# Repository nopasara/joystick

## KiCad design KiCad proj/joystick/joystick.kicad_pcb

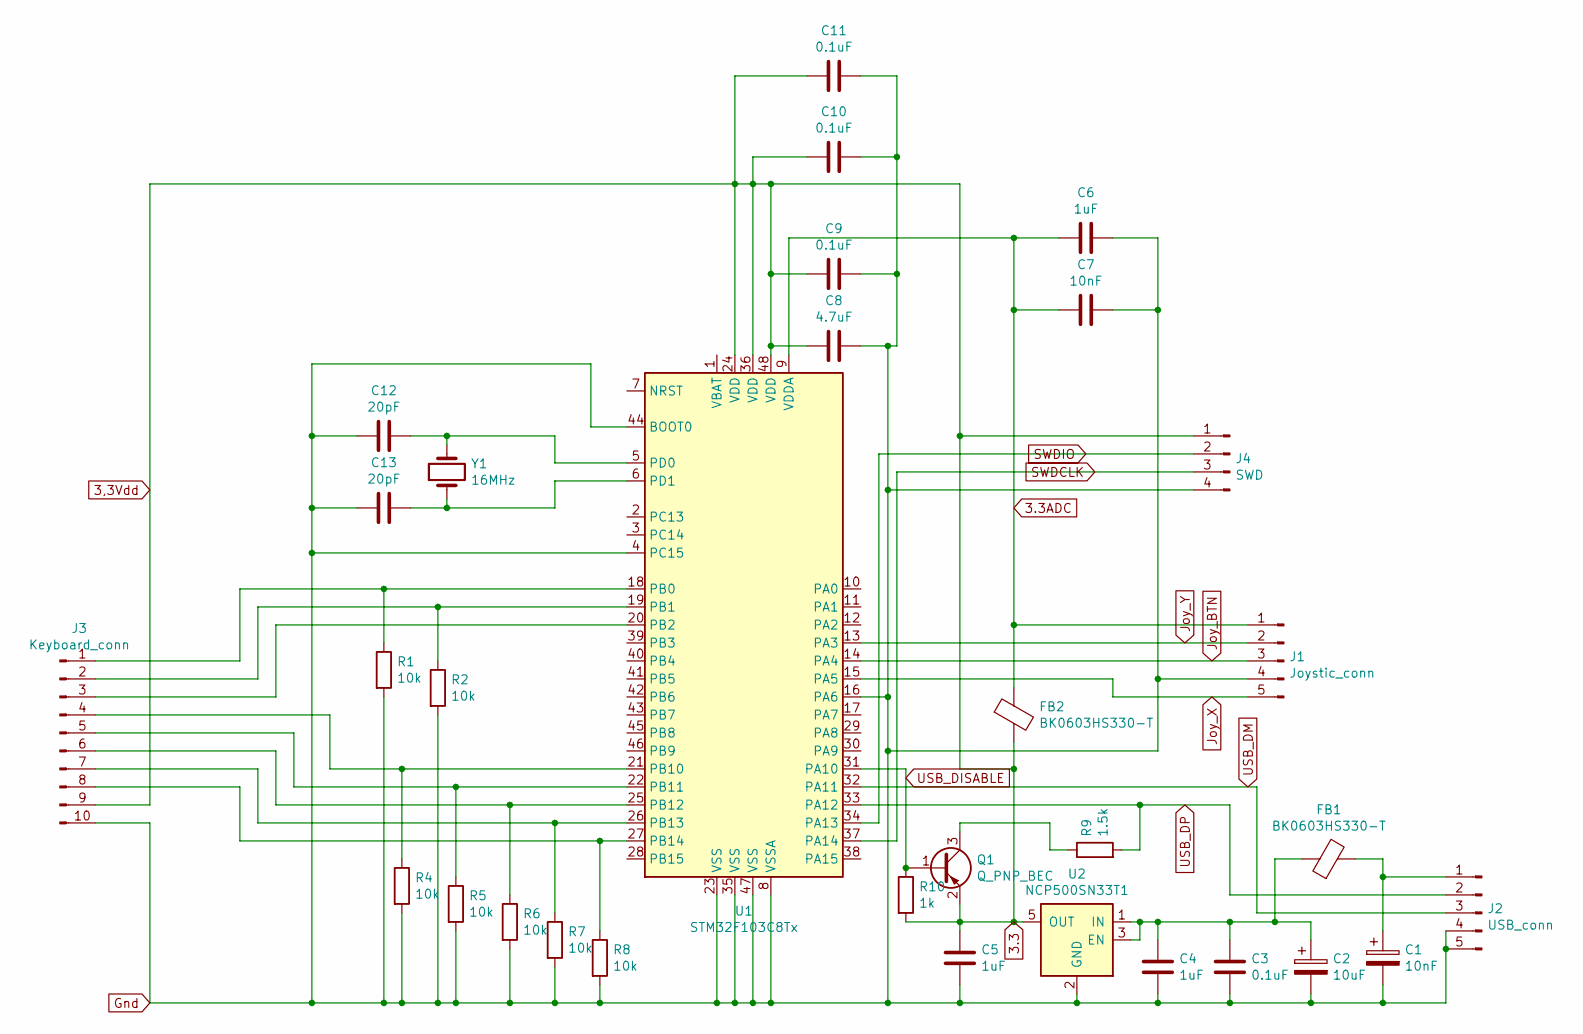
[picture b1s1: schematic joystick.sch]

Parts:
C1, C7: 10nF; C_0603_1608Metric_Pad1.08x0.95mm_HandSolder
C2: 10uF; CP_Radial_D5.0mm_P2.50mm
C3, C9, C10, C11: 0.1uF; C_0805_2012Metric_Pad1.18x1.45mm_HandSolder
C4, C5, C6: 1uF; C_0805_2012Metric_Pad1.18x1.45mm_HandSolder
C8: 4.7uF; CP_Radial_D5.0mm_P2.50mm
C12, C13: 20pF; C_0603_1608Metric_Pad1.08x0.95mm_HandSolder
FB1, FB2: BK0603HS330-T; R_0603_1608Metric_Pad0.98x0.95mm_HandSolder
J1: Joystic_conn; FPC-5P-0.5mm
J2: USB_conn; PinHeader_1x05_P2.54mm_Vertical
J3: Keyboard_conn; Hirose_FH12-10S-0.5SH_1x10-1MP_P0.50mm_Horizontal
J4: SWD; PinHeader_1x04_P2.54mm_Vertical
Q1: Q_PNP_BEC; SOT-23
R1, R2, R4, R5, R6, R7, R8: 10k; R_0201_0603Metric_Pad0.64x0.40mm_HandSolder
R9: 1.5k; C_0805_2012Metric_Pad1.18x1.45mm_HandSolder
R10: 1k; R_0603_1608Metric_Pad0.98x0.95mm_HandSolder
U1: STM32F103C8Tx; LQFP-48_7x7mm_P0.5mm
U2: NCP500SN33T1; TSOP-5_1.65x3.05mm_P0.95mm
Y1: 16MHz; Crystal_HC49-S_Vertical

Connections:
3,3Vdd: C5.1, C8.1, C9.1, C10.1, C11.1, FB2.2, J3.9, J4.1, Q1.2 (E), R10.2, U1.24 (VDD), U1.36 (VDD), U1.48 (VDD), U2.5 (OUT)
3.3ADC: C6.1, C7.1, FB2.1, J1.1, U1.9 (VDDA)
Gnd: C1.2, C2.2, C3.2, C4.2, C5.2, C6.2, C7.2, C8.2, C9.2, C10.2, C11.2, C12.1, C13.1, J1.4, J2.4, J2.5, J3.10, J4.4, R1.2, R2.2, R4.2, R5.2, R6.2, R7.2, R8.2, U1.4 (PC15), U1.8 (VSSA), U1.16 (PA6), U1.23 (VSS), U1.35 (VSS), U1.44 (BOOT0), U1.47 (VSS), U2.2 (GND)
Joy_BTN: J1.3, U1.14 (PA4)
Joy_X: J1.5, U1.15 (PA5)
Joy_Y: J1.2, U1.13 (PA3)
unnamed: C1.1, FB1.2, J2.1
unnamed: C2.1, C3.1, C4.1, FB1.1, U2.1 (IN), U2.3 (EN)
unnamed: C12.2, U1.5 (PD0), Y1.2
unnamed: C13.2, U1.6 (PD1), Y1.1
unnamed: J3.1, R1.1, U1.18 (PB0)
unnamed: J3.2, R2.1, U1.19 (PB1)
unnamed: J3.3, U1.20 (PB2)
unnamed: J3.4, R4.1, U1.21 (PB10)
unnamed: J3.5, R5.1, U1.22 (PB11)
unnamed: J3.6, R6.1, U1.25 (PB12)
unnamed: J3.7, R7.1, U1.26 (PB13)
unnamed: J3.8, R8.1, U1.27 (PB14)
unnamed: Q1.3 (C), R9.1
SWDCLK: J4.3, U1.37 (PA14)
SWDIO: J4.2, U1.34 (PA13)
USB_DISABLE: Q1.1 (B), R10.1, U1.31 (PA10)
USB_DM: J2.3, U1.32 (PA11)
USB_DP: J2.2, R9.2, U1.33 (PA12)

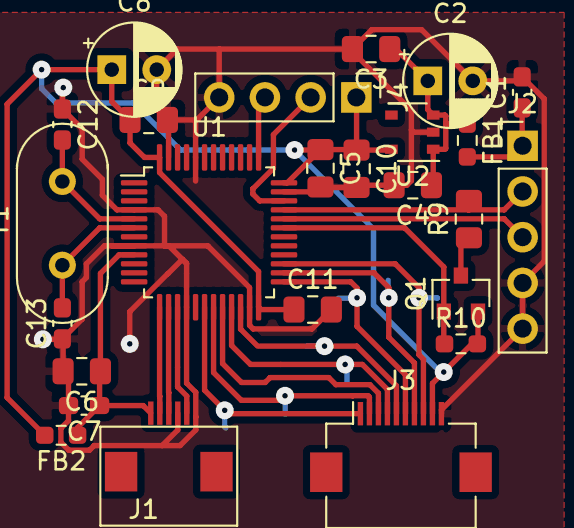
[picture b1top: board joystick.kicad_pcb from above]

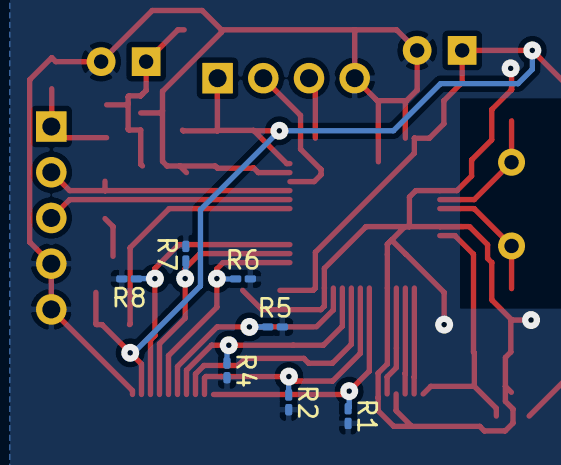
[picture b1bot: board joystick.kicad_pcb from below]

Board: 2 copper layers, 32 parts (7 on the bottom side), 24 nets.

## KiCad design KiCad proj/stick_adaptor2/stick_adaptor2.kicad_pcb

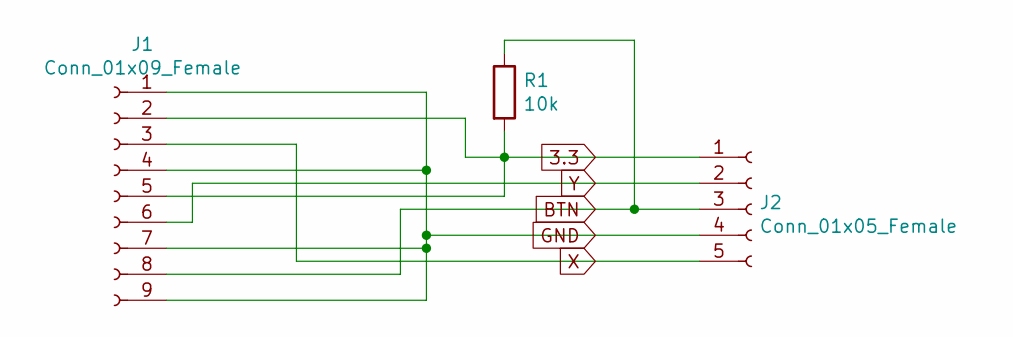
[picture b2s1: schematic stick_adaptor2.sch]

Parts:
J1: Conn_01x09_Female; Stick_china
J2: Conn_01x05_Female; PinHeader_1x05_P1.27mm_Vertical
R1: 10k; R_0603_1608Metric_Pad0.98x0.95mm_HandSolder

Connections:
3.3: J1.2, J1.5, J2.1, R1.2
BTN: J1.8, J2.3, R1.1
GND: J1.1, J1.4, J1.7, J1.9, J2.4
X: J1.3, J2.5
Y: J1.6, J2.2

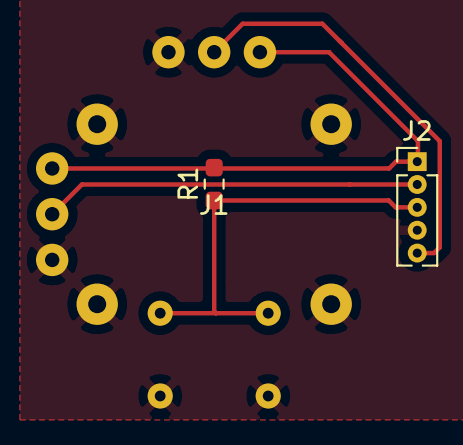
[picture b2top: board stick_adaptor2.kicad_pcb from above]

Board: 2 copper layers, 3 parts (0 on the bottom side), 5 nets.

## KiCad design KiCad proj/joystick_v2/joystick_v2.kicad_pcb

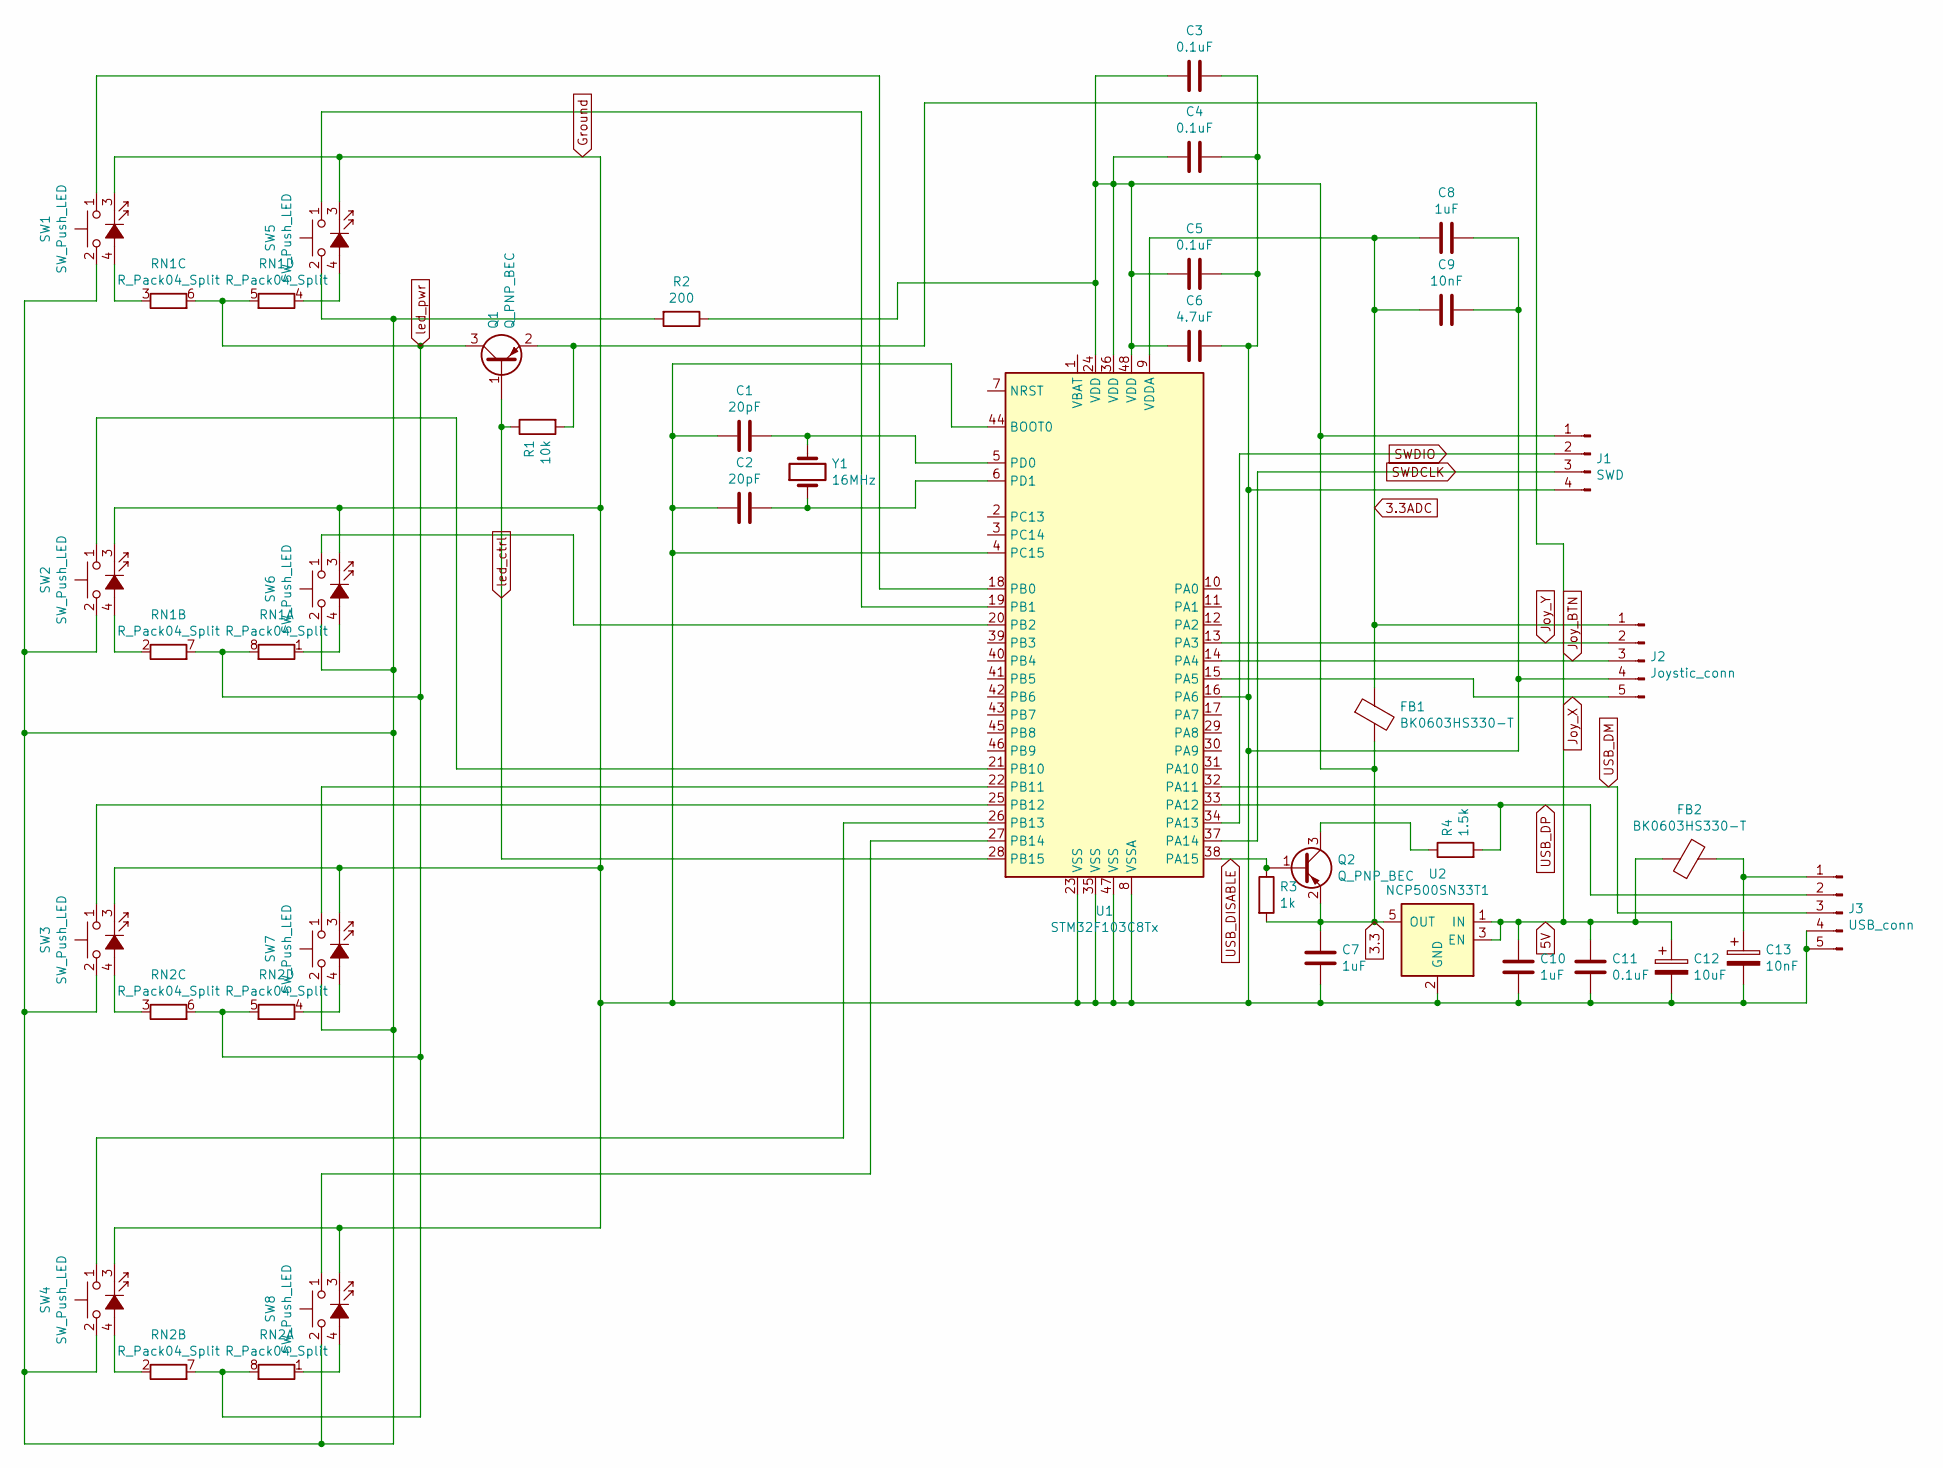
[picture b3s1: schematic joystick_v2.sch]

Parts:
C1, C2: 20pF; C_0603_1608Metric_Pad1.08x0.95mm_HandSolder
C3, C4, C5, C11: 0.1uF; C_0805_2012Metric_Pad1.18x1.45mm_HandSolder
C6: 4.7uF; CP_Radial_D5.0mm_P2.50mm
C7, C8, C10: 1uF; C_0805_2012Metric_Pad1.18x1.45mm_HandSolder
C9, C13: 10nF; C_0603_1608Metric_Pad1.08x0.95mm_HandSolder
C12: 10uF; CP_Radial_D5.0mm_P2.50mm
FB1, FB2: BK0603HS330-T; R_0603_1608Metric_Pad0.98x0.95mm_HandSolder
J1: SWD; PinHeader_1x04_P2.54mm_Vertical
J2: Joystic_conn; PinHeader_1x05_P1.27mm_Vertical
J3: USB_conn; PinHeader_1x05_P2.54mm_Vertical
Q1, Q2: Q_PNP_BEC; SOT-23
R1: 10k; R_0603_1608Metric_Pad0.98x0.95mm_HandSolder
R2: 200; R_0603_1608Metric_Pad0.98x0.95mm_HandSolder
R3: 1k; R_0603_1608Metric_Pad0.98x0.95mm_HandSolder
R4: 1.5k; C_0805_2012Metric_Pad1.18x1.45mm_HandSolder
RN1, RN2: R_Pack04_Split; R_Cat16-4
SW1, SW2, SW3, SW4, SW5, SW6, SW7, SW8: SW_Push_LED; SW_Cherry_MX_1.00u_Plate_diode
U1: STM32F103C8Tx; LQFP-48_7x7mm_P0.5mm
U2: NCP500SN33T1; TSOP-5_1.65x3.05mm_P0.95mm
Y1: 16MHz; Crystal_HC49-S_Vertical

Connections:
3.3: C3.1, C4.1, C5.1, C6.1, C7.1, FB1.2, J1.1, Q2.2 (E), R2.1, R3.2, U1.24 (VDD), U1.36 (VDD), U1.48 (VDD), U2.5 (OUT)
3.3ADC: C8.1, C9.1, FB1.1, J2.1, U1.9 (VDDA)
5V: C10.1, C11.1, C12.1, FB2.1, Q1.2 (E), R1.2, U2.1 (IN), U2.3 (EN)
Ground: C1.1, C2.1, C3.2, C4.2, C5.2, C6.2, C7.2, C8.2, C9.2, C10.2, C11.2, C12.2, C13.2, J1.4, J2.4, J3.4, J3.5, SW1.3 (K), SW2.3 (K), SW3.3 (K), SW4.3 (K), SW5.3 (K), SW6.3 (K), SW7.3 (K), SW8.3 (K), U1.4 (PC15), U1.8 (VSSA), U1.16 (PA6), U1.23 (VSS), U1.35 (VSS), U1.44 (BOOT0), U1.47 (VSS), U2.2 (GND)
Joy_BTN: J2.3, U1.14 (PA4)
Joy_X: J2.5, U1.15 (PA5)
Joy_Y: J2.2, U1.13 (PA3)
unnamed: C1.2, U1.5 (PD0), Y1.2
unnamed: C2.2, U1.6 (PD1), Y1.1
unnamed: C13.1, FB2.2, J3.1
unnamed: Q2.3 (C), R4.1
unnamed: R2.2, SW1.2, SW2.2, SW3.2, SW4.2, SW5.2, SW6.2, SW7.2, SW8.2
unnamed: RN1.1 (R1.1), SW6.4 (A)
unnamed: RN1.2 (R2.1), SW2.4 (A)
unnamed: RN1.3 (R3.1), SW1.4 (A)
unnamed: RN1.4 (R4.1), SW5.4 (A)
unnamed: RN2.1 (R1.1), SW8.4 (A)
unnamed: RN2.2 (R2.1), SW4.4 (A)
unnamed: RN2.3 (R3.1), SW3.4 (A)
unnamed: RN2.4 (R4.1), SW7.4 (A)
unnamed: SW1.1, U1.18 (PB0)
unnamed: SW2.1, U1.21 (PB10)
unnamed: SW3.1, U1.25 (PB12)
unnamed: SW4.1, U1.26 (PB13)
unnamed: SW5.1, U1.19 (PB1)
unnamed: SW6.1, U1.20 (PB2)
unnamed: SW7.1, U1.22 (PB11)
unnamed: SW8.1, U1.27 (PB14)
SWDCLK: J1.3, U1.37 (PA14)
SWDIO: J1.2, U1.34 (PA13)
USB_DISABLE: Q2.1 (B), R3.1, U1.38 (PA15)
USB_DM: J3.3, U1.32 (PA11)
USB_DP: J3.2, R4.2, U1.33 (PA12)
led_ctrl: Q1.1 (B), R1.1, U1.28 (PB15)
led_pwr: Q1.3 (C), RN1.5 (R4.2), RN1.6 (R3.2), RN1.7 (R2.2), RN1.8 (R1.2), RN2.5 (R4.2), RN2.6 (R3.2), RN2.7 (R2.2), RN2.8 (R1.2)

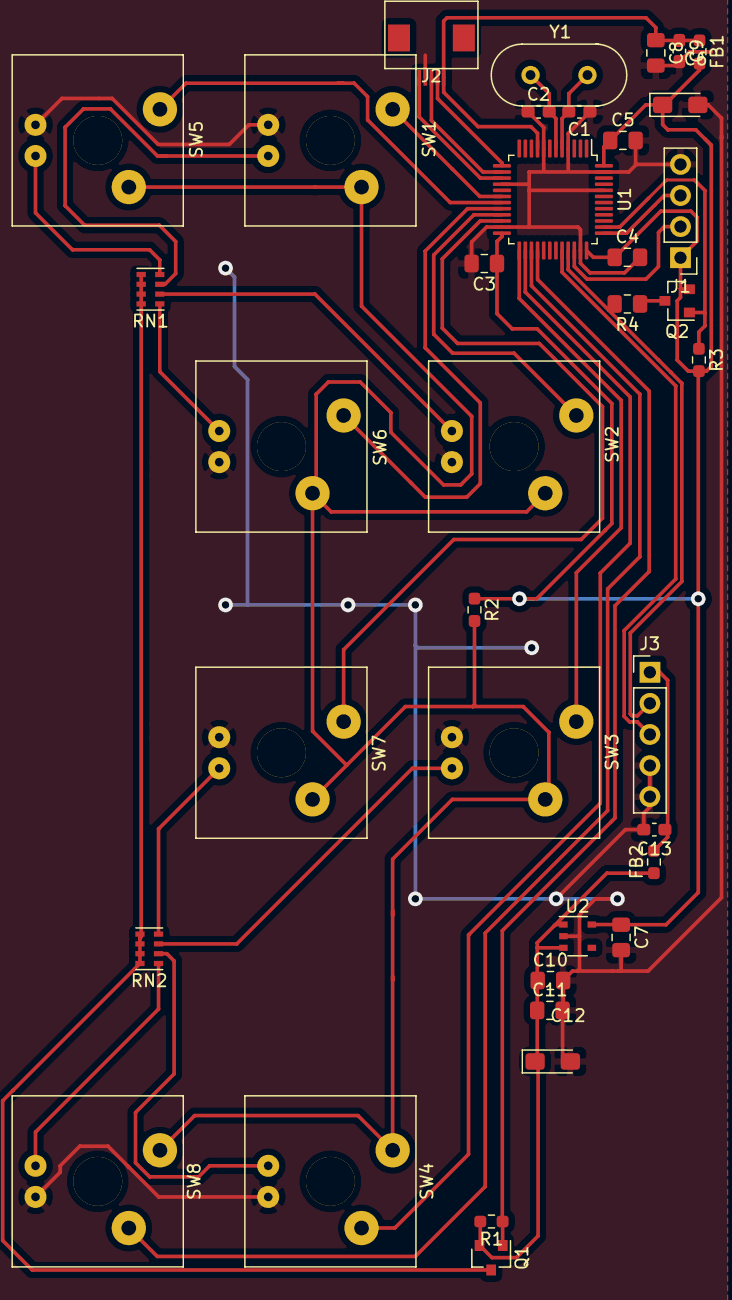
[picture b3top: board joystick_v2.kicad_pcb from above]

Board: 2 copper layers, 37 parts (0 on the bottom side), 35 nets.

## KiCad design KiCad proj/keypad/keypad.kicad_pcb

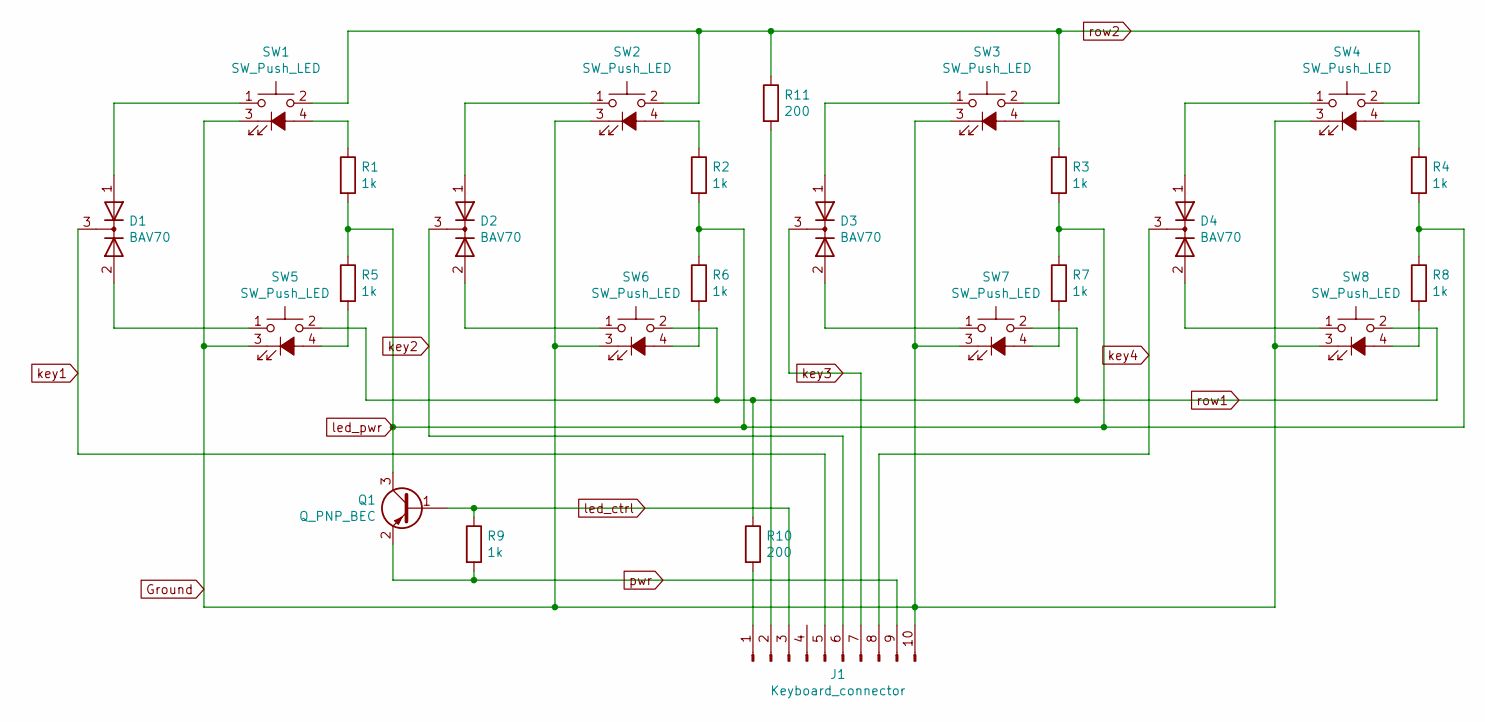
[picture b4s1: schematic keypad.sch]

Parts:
D1, D2, D3, D4: BAV70; SOT-23
J1: Keyboard_connector; Hirose_FH12-10S-0.5SH_1x10-1MP_P0.50mm_Horizontal
Q1: Q_PNP_BEC; SOT-23
R1, R2, R3, R4, R5, R6, R7, R8, R9: 1k; R_0603_1608Metric_Pad0.98x0.95mm_HandSolder
R10, R11: 200; R_0603_1608Metric_Pad0.98x0.95mm_HandSolder
SW1, SW2, SW3, SW4, SW5, SW6, SW7, SW8: SW_Push_LED; PinHeader_1x04_P2.54mm_Vertical

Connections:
Ground: J1.10, SW1.3 (K), SW2.3 (K), SW3.3 (K), SW4.3 (K), SW5.3 (K), SW6.3 (K), SW7.3 (K), SW8.3 (K)
unnamed: D1.1 (A), SW1.1
unnamed: D1.2 (A), SW5.1
unnamed: D2.1 (A), SW2.1
unnamed: D2.2 (A), SW6.1
unnamed: D3.1 (A), SW3.1
unnamed: D3.2 (A), SW7.1
unnamed: D4.1 (A), SW4.1
unnamed: D4.2 (A), SW8.1
unnamed: J1.1, R10.2
unnamed: J1.2, R11.2
unnamed: R1.1, SW1.4 (A)
unnamed: R2.1, SW2.4 (A)
unnamed: R3.1, SW3.4 (A)
unnamed: R4.1, SW4.4 (A)
unnamed: R5.2, SW5.4 (A)
unnamed: R6.2, SW6.4 (A)
unnamed: R7.2, SW7.4 (A)
unnamed: R8.2, SW8.4 (A)
key1: D1.3 (K), J1.5
key2: D2.3 (K), J1.6
key3: D3.3 (K), J1.7
key4: D4.3 (K), J1.8
led_ctrl: J1.3, Q1.1 (B), R9.1
led_pwr: Q1.3 (C), R1.2, R2.2, R3.2, R4.2, R5.1, R6.1, R7.1, R8.1
pwr: J1.9, Q1.2 (E), R9.2
row1: R10.1, SW5.2, SW6.2, SW7.2, SW8.2
row2: R11.1, SW1.2, SW2.2, SW3.2, SW4.2

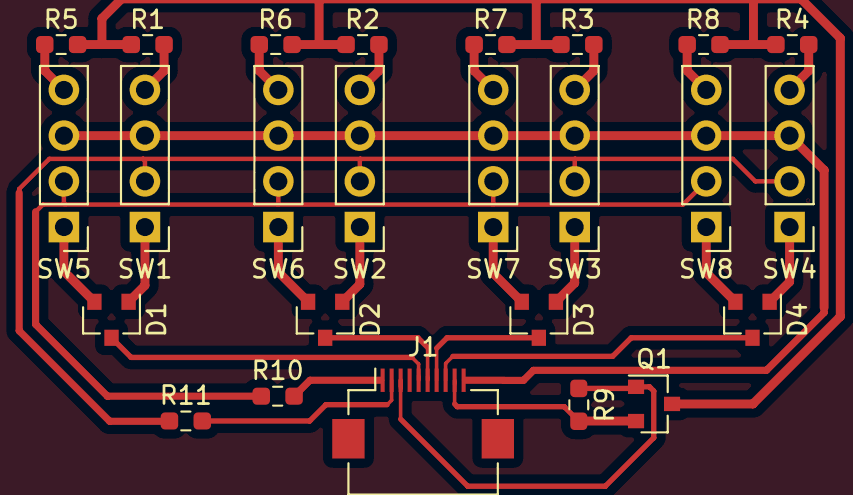
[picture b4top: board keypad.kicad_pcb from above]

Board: 2 copper layers, 25 parts (0 on the bottom side), 28 nets.

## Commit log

2021-08-06 Initial joystick project commit
    The USB joystick project on the STM32F103 MCU that consists of a JoyCon
    stick and 8 keyboard switches. The project contains the firmware and
    KiCad project with shcemas
2021-09-19 Add labels to keyboard pins
    Add labels to keyboard pins in order to have explicit key->port B pins
    mapping
2021-09-19 Enhance comment
    Make comment more meaningful
2021-09-19 Fix KeyMap indexing
    Fix the operation order by adding braces and add incremental key index
    calculation logic
2021-09-19 Remove swap files
    Remove swap files commited by mistake
2021-09-19 Fix key mappings
    Fix the key mappings and descriptor in order to match 1-8 charecter
    range
2021-09-19 Fix Makefile
    Fix the clean rule in order to remove the .map file
    Introduce project name variable used as a base of the bianry and map
    filenames
2022-01-29 Add new joystick shcematics
    Add schematics for keyboard and jouystick adaptors
2022-01-29 Updated code for the new schematics
2022-01-29 Remove autogenerated files
    Remove backup and generated files from repo
